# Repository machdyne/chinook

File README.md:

# Chinook Computer

Chinook is a metacomputer designed by Lone Dynamics Corporation.

This repo will contain schematics, PCB layouts, pinouts, a 3D-printable case and documentation.

Find more information on the [Chinook product page](https://machdyne.com/product/chinook-computer/).

## Bootloader

Chinook uses the [rv003usb](https://github.com/cnlohr/rv003usb) bootloader to support firmware updates over the USB-C connector. If overwritten, it can be restored with the SWIO pin and an external programmer.

## Linux

Chinook uses a slightly modified [fork](https://github.com/machdyne/linux-ch32v003) of [linux-ch32v003](https://github.com/tvlad1234/linux-ch32v003).

Build with `make -f Makefile.chinook`.

## Power

Chinook can be powered through the barrel jack connector (or the PWRJACK pin) or the USB-C connector.

## Pinouts

### Left connector

This connector is compatible with HC-05/06 bluetooth modules, make sure the pins match the pinout below when plugging the module in (it may need to be upside down).

| Pin | Signal | Description |
| --- | ------ | ----------- |
| 1 | NC | not connected |
| 2 | TX | MCU UART transmit / bluetooth RX |
| 3 | RX | MCU UART receive / bluetooth TX |
| 4 | GND | Ground |
| 5 | PWR5V0 | 5V output |
| 6 | HCEN | High = HC-05/06 UART mode, Low = AT comamnd mode |

### Right connector

This connector is for general purpose I/O and optional power input/output.

| Pin | Signal | Description |
| --- | ------ | ----------- |
| 1 | GPIOA | GPIO / I2C SCL |
| 2 | GPIOB | GPIO / I2C SDA |
| 3 | GPIOC | GPIO / ADC1 |
| 4 | GPIOD | GPIO / ADC0 |
| 5 | SWIO | MCU programming pin |
| 6 | GND | Ground |
| 7 | PWR3V3 | 3.3V output |
| 8 | PWRJACK | Power input (9-15V) connected to barrel jack |

## License

The contents of this repo are released under the [Lone Dynamics Open License](LICENSE.md).

Note: You can use these designs for commercial purposes but we ask that instead of producing exact clones, that you either replace our trademarks and logos with your own or add your own next to ours.

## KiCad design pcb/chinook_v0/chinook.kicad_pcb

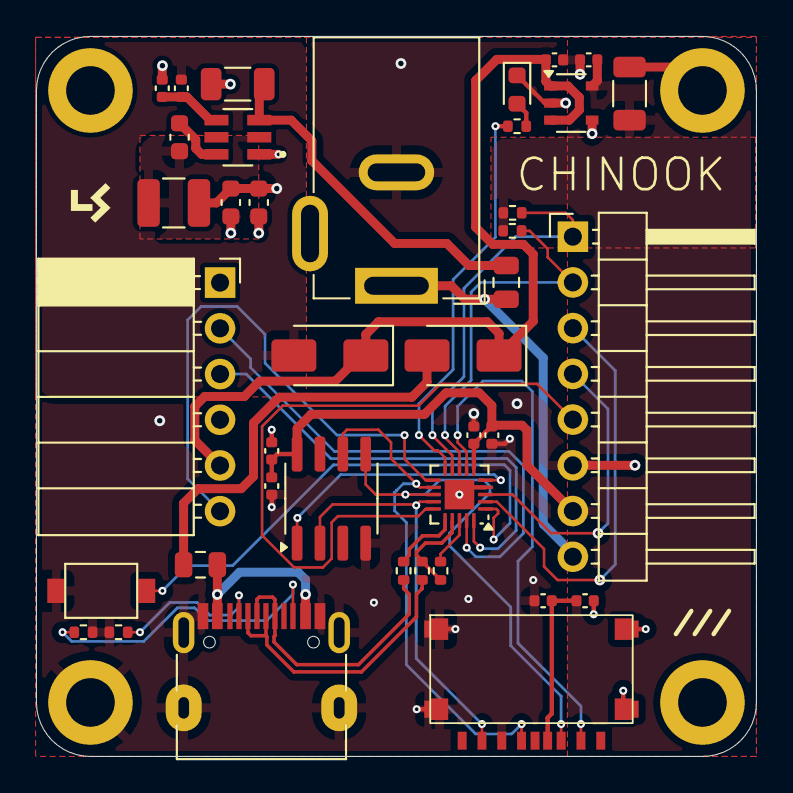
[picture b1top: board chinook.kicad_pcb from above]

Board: 2 copper layers, 40.0 x 40.0 mm, 43 parts (0 on the bottom side), 34 nets.

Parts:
C1, C5, C7: 100nF; C_0402_1005Metric
C2, C4: 10uF; C_0402_1005Metric
C6, C8, C14: 1uF; C_0402_1005Metric
C9: 10uF50v; C_1206_3216Metric
C10: 100nF50v; C_0603_1608Metric
C11, C12: 22uF; C_0603_1608Metric
C13: 100uF; C_1206_3216Metric
D1: LED; LED_0603_1608Metric
D2, D3: DSS34; D_SMA
F1, F2: 500mA; Fuse_0805_2012Metric
H1, H2, H3, H4: MountingHole_Pad; MountingHole_2.7mm_M2.5_DIN965_Pad
J1: USB_C_Receptacle_USB2.0_14P; USB_C_Receptacle_HRO_TYPE-C-31-M-12-BIG-PADS-PASTE
J2: MICROSD; TF-018B-H15-HAND-SOLDER
J3: Barrel_Jack; BarrelJack_GCT_DCJ200-10-A_Horizontal
J4: Conn_01x06_Socket; PinSocket_1x06_P2.54mm_Horizontal
J5: Conn_01x08_Pin; PinHeader_1x08_P2.54mm_Horizontal
L1: 3.3uH; L_1210_3225Metric
R1, R5: 1K5; R_0402_1005Metric
R2, R3: 33R; R_0402_1005Metric
R4, R6: 4.7K; R_0402_1005Metric
R7, R8: 5K1; R_0402_1005Metric
R11: 56K2; C_0402_1005Metric
R12: 10K; C_0402_1005Metric
SW1: SW_Push; Button_2P_3x4mm
U1: CH32V003FxUx; QFN-20-1EP_3x3mm_P0.4mm_EP1.65x1.65mm
U2: AP62300TWU-7; SOT95P280X100-6N
U3: ESP-PSRAM32; SOIC-8_3.9x4.9mm_P1.27mm
U4: NCP115; TSOP-5_1.65x3.05mm_P0.95mm

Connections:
/GPIOA: J5.1, R4.1, U1.9 (PC2)
/GPIOB: J5.2, R6.1, U1.8 (PC1)
/GPIOC: J5.3, U1.2 (PA1)
/GPIOD: J5.4, U1.3 (PA2)
/HCEN: J4.6, U1.11 (PC4)
/LED: R1.2, U1.10 (PC3)
/MISO: J2.7 (DAT0), U1.14 (PC7), U3.2 (SO/SIO)
/MOSI: J2.3 (CMD), U1.13 (PC6), U3.5 (SI/SIO)
/PWR3V3: C1.1, C2.1, C4.1, C5.1, C7.1, C8.1, C13.1, C14.1, J2.4 (VDD), J5.7, R4.2, R6.2, U1.6 (VDD), U3.8 (VCC), U4.5 (OUT)
/PWR5V0: C6.1, D2.1 (K), D3.1 (K), J4.5, U4.1 (IN), U4.3 (EN)
/PWRBUCK: C11.1, C12.1, D2.2 (A), L1.2, R11.2
/PWRFJACK: F1.1, J3.1, J5.8
/PWRFVBUS: F2.1, J1.A4 (VBUS), J1.A9 (VBUS), J1.B4 (VBUS), J1.B9 (VBUS)
/PWRJACK: C9.1, F1.2, U2.3 (VIN)
/PWRVBUS: D3.2 (A), F2.2
/RESET: SW1.1, U1.1 (PD7)
/SCK: J2.5 (CLK), U1.12 (PC5), U3.6 (SCLK)
/SS_PSRAM: U1.5 (PD0), U3.1 (~CE)
/SS_SD: J2.2 (DAT3/CD), U1.7 (PC0)
/SW: C10.2, L1.1, U2.2 (SW)
/SWIO: J5.5, U1.15 (PD1)
/UART_RX: J4.3, U1.20 (PD6)
/UART_TX: J4.2, U1.19 (PD5)
/USB_CONN_CC1: J1.A5 (CC1), R7.2
/USB_CONN_CC2: J1.B5 (CC2), R8.2
/USB_CONN_DN: J1.A7 (D-), J1.B7 (D-), R2.1
/USB_CONN_DP: J1.A6 (D+), J1.B6 (D+), R3.1
/USB_DN: R2.2, R5.1, U1.17 (PD3)
/USB_DN_PU: R5.2, U1.18 (PD4)
/USB_DP: R3.2, U1.16 (PD2)
GND: C1.2, C2.2, C4.2, C5.2, C6.2, C7.2, C8.2, C9.2, C11.2, C12.2, C13.2, C14.2, D1.1 (K), H1.1, H2.1, H3.1, H4.1, J1.A1 (GND), J1.A12 (GND), J1.B1 (GND), J1.B12 (GND), J1.S1 (SHIELD), J2.6 (VSS), J3.2, J4.4, J5.6, R7.1, R8.1, R12.1, SW1.2, U1.4 (VSS), U1.21 (VSS), U2.1 (GND), U3.4 (VSS), U4.2 (GND), U4.4 (GND2)
unnamed: D1.2 (A), R1.1
unnamed: C10.1, U2.6 (BST)
unnamed: R11.1, R12.2, U2.4 (FB)
